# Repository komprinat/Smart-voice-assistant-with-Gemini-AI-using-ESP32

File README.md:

# Smart voice assistant with Gemini AI using ESP32
## Alur kerja sistem
- Voice input menggunakan INMP441
- ESP32 sebagai perangkat utama
- WebSocket untuk komunikasi audio
- Speech-to-Text menggunakan speech recognition
- Gemini AI
- Text-to-Speech menggunakan Piper dengan [model bahasa indonesia](/server/model_tts)
- MQTT untuk komunikasi data sensor

## Rangkaian ESP32

### Library yang digunakan
Code pada ESP32 dibuat menggunakan Platformio dengan [code](/ESP32/src/main.cpp) serta menggunakan [library](/ESP32/platformio.ini)
* [ArduinoWebscoket by gilmaimon](https://github.com/gilmaimon/ArduinoWebsockets)
* [DHT sensor library by adafruit](https://github.com/adafruit/dht-sensor-library)
* [MQSpaceData by abcdaaaaaaaaa](https://github.com/abcdaaaaaaaaa/MQDataScience?utm_source=pioarduino)
* [PubSubClient by knolleary](https://github.com/knolleary/pubsubclient?utm_source=pioarduino)

## Server
Server menggunakan python 3.13 dan Broker MQTT Mosquitto. Pastikan semua library yang ada di [requirements](/server/requirements.txt) sudah terinstall baik secara global atau di virtual environment. Pastikan sudah mengisi API Key Gemini di [kode](/server/config.py) yang bisa didapat di [sini](https://aistudio.google.com/api-keys). Untuk Menjalankan server klik run.bat dengan mode administrator dan ketik server on

## Hardware dan yang lainnya
### PCB
PCB dibuat menggunakan software KiCad untuk [desain](/Perancangan/PCB/TA.kicad_pcb) serta [skematiknya](/Perancangan/PCB/TA.kicad_sch) dan pabrikasi dilakukan dengan metode toner pada PCB single layer

### Desain kotak

[Desain](/Perancangan/3D%20Printing%20Design/Untuk%20TA2.FCStd) dibuat menggunakan FreeCAD 3D Printing menggunakan filamen PLA+ dengan infill 15% dan layer height 0,2mm

## Bug dan Error yang ada
* Koneksi antara ESP32 dan server kadang terputus
* Suara kadang freeze

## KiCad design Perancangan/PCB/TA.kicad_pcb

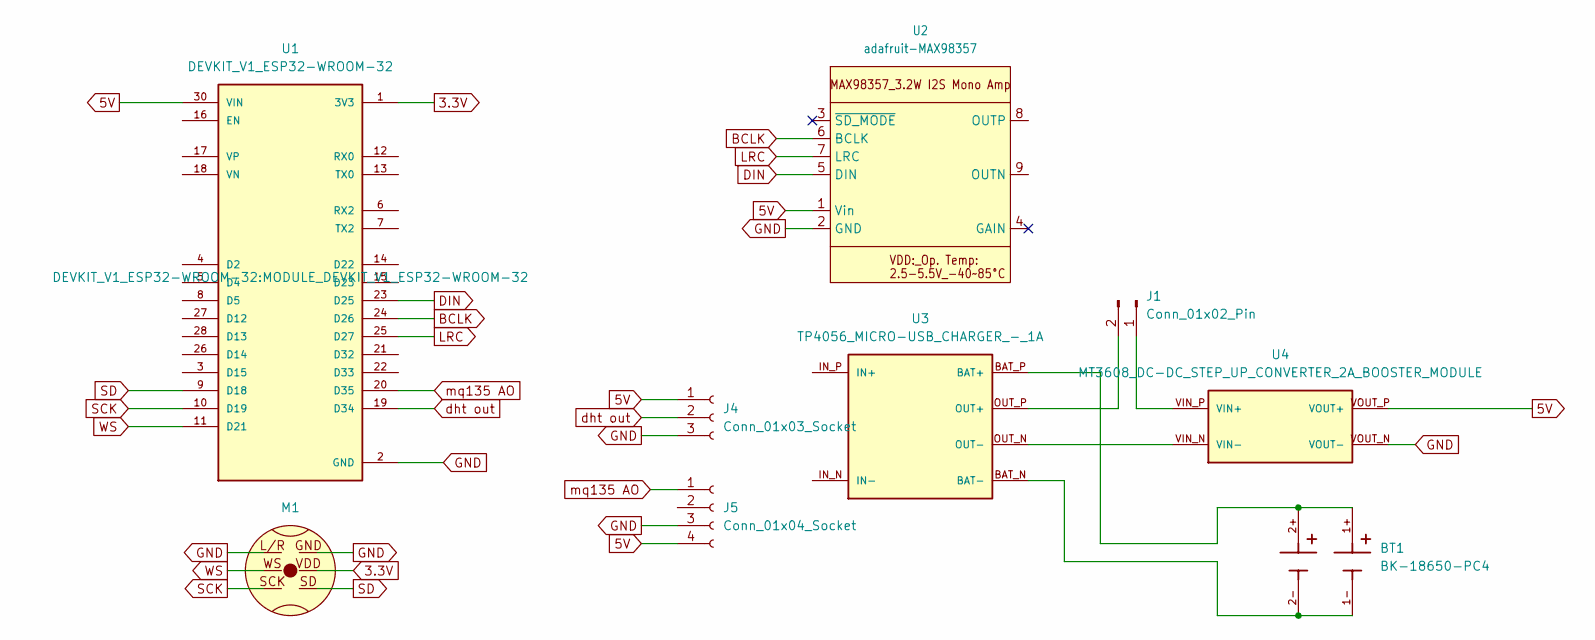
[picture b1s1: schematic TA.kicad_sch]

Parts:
BT1: BK-18650-PC4; BAT_BK-18650-PC4; PARTREV K
J1: Conn_01x02_Pin; PinSocket_1x02_P2.54mm_Vertical
J4: Conn_01x03_Socket; PinSocket_1x03_P2.54mm_Horizontal
J5: Conn_01x04_Socket; PinSocket_1x04_P2.54mm_Horizontal
M1: INMP441
U1: DEVKIT_V1_ESP32-WROOM-32; MODULE_DEVKIT_V1_ESP32-WROOM-32
U2: adafruit-MAX98357
U3: TP4056_MICRO-USB_CHARGER_-_1A; MODULE_TP4056_MICRO-USB_CHARGER_-_1A
U4: MT3608_DC-DC_STEP_UP_CONVERTER_2A_BOOSTER_MODULE; MODULE_MT3608_DC-DC_STEP_UP_CONVERTER_2A_BOOSTER_MODULE

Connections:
3.3V: M1.VDD, U1.1 (3V3)
5V: J4.1, J5.4, U1.30 (VIN), U2.1 (Vin), U4.VOUT_P (VOUT+)
BCLK: U1.24 (D26), U2.6 (BCLK)
DIN: U1.23 (D25), U2.5 (DIN)
GND: J4.3, J5.3, M1.GND, M1.L/R, U1.2 (GND), U1.29 (GND), U2.2 (GND), U4.VOUT_N (VOUT-)
LRC: U1.25 (D27), U2.7 (LRC)
unnamed: J1.1, U4.VIN_P (VIN+)
unnamed: J1.2, U3.OUT_P (OUT+)
unnamed: BT1.1+, BT1.2+, U3.BAT_P (BAT+)
unnamed: BT1.1-, BT1.2-, U3.BAT_N (BAT-)
unnamed: U3.OUT_N (OUT-), U4.VIN_N (VIN-)
SCK: M1.SCK, U1.10 (D19)
SD: M1.SD, U1.9 (D18)
WS: M1.WS, U1.11 (D21)
dht out: J4.2, U1.19 (D34)
mq135 AO: J5.1, U1.20 (D35)

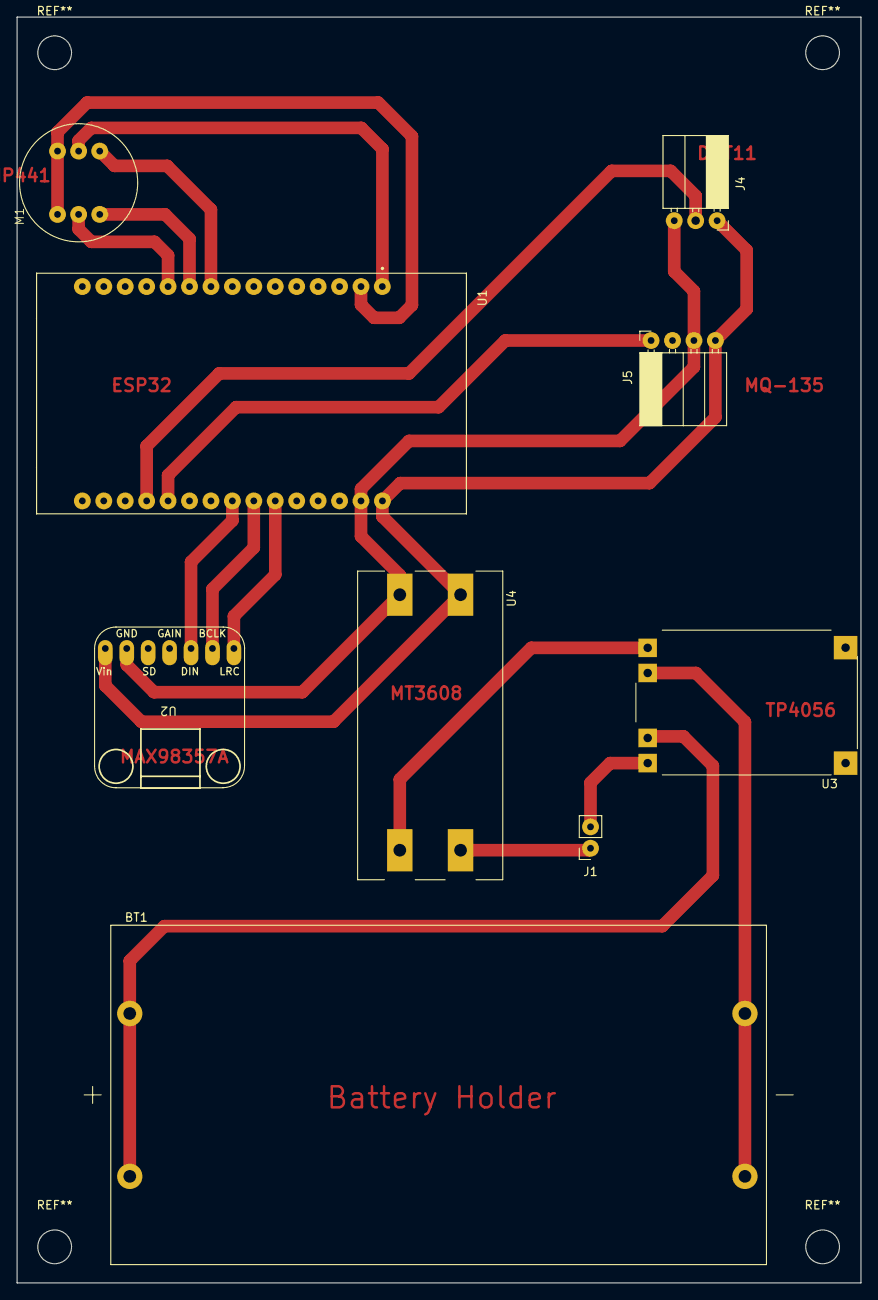
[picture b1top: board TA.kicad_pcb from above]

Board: 2 copper layers, 100.0 x 150.0 mm, 9 parts (0 on the bottom side), 16 nets.
